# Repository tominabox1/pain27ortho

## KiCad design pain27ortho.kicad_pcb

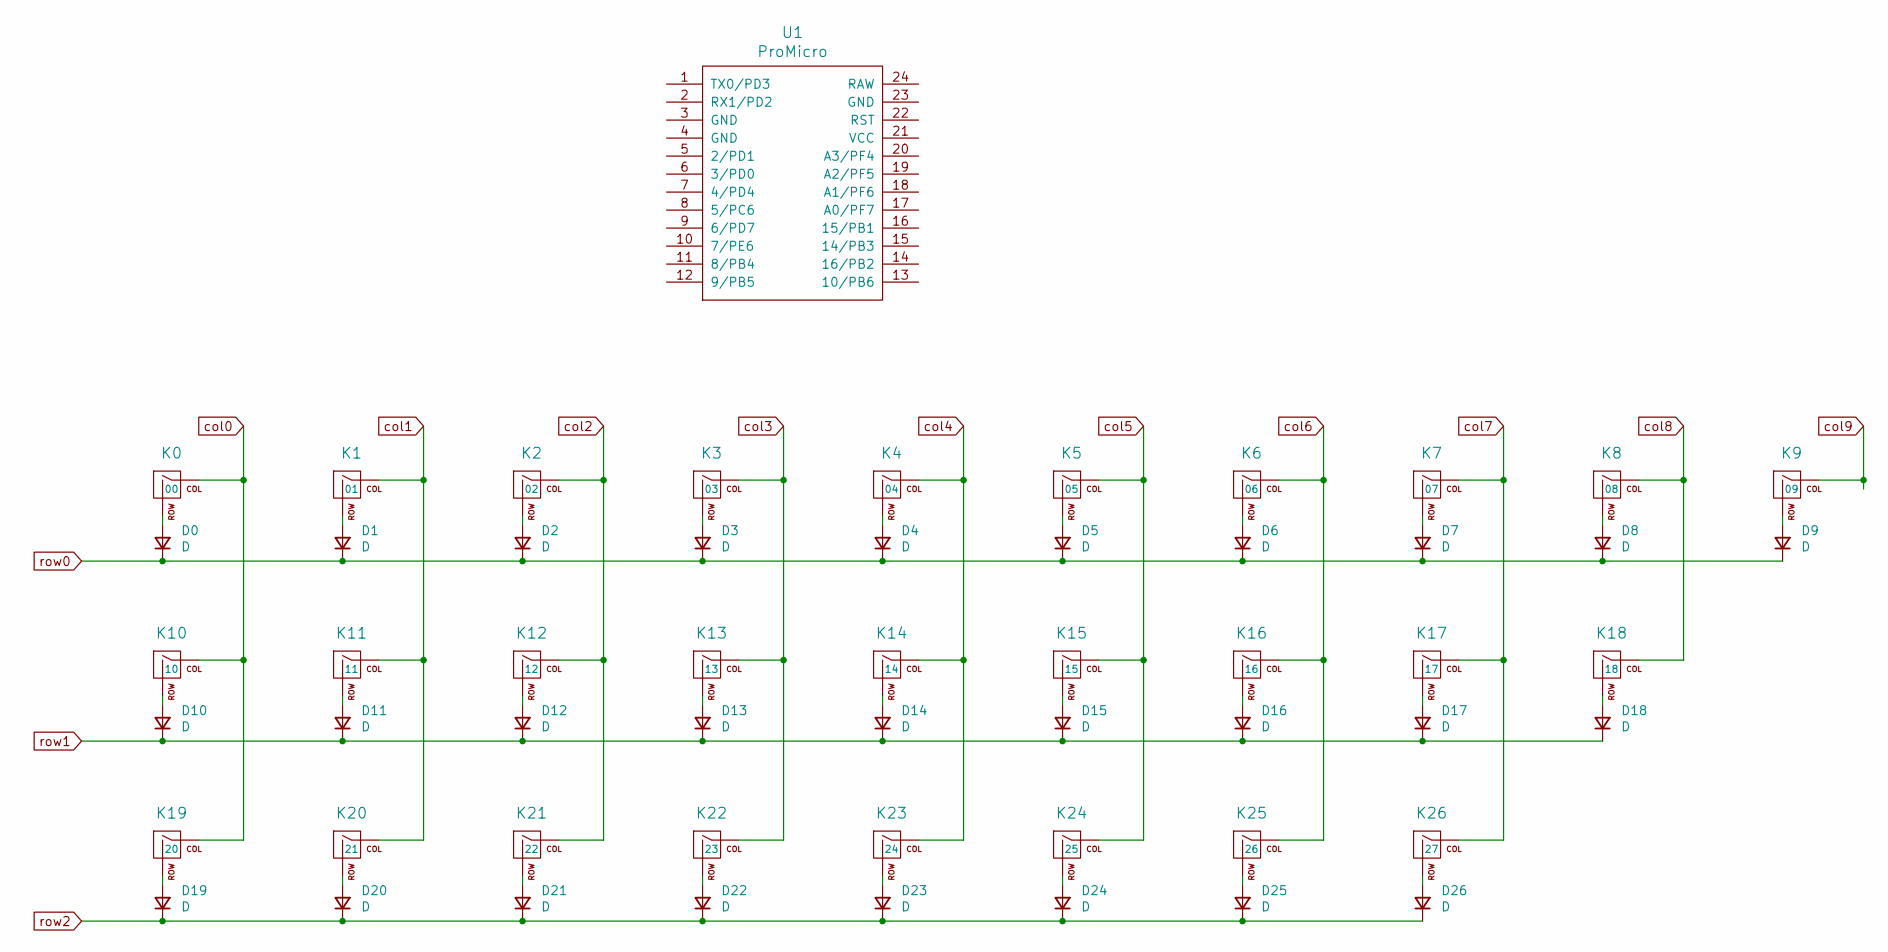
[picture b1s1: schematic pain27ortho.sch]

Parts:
D0, D1, D2, D3, D4, D5, D6, D7, D8, D9, D10, D11, D12, D13, D14, D15, D16, D17, D18, D19, D20, D21, D22, D23, D24, D25, D26: D; Diode-Hybrid-Back
K0, K1, K2, K3, K4, K5, K6, K7, K8, K9, K10, K11, K12, K13, K14, K15, K16, K17, K18, K19, K20, K21, K22, K23, K24, K25: 1U; MXOnly-1U-NoLED
K26: 6.25U; MXOnly-6.25U-NoLED
U1: ProMicro; ArduinoProMicro

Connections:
/Data: U1.8 (5/PC6); also elsewhere on the board
GND: U1.3 (GND), U1.4 (GND), U1.23 (GND); also elsewhere on the board
unnamed: D0.2 (A), K0.2 (ROW)
unnamed: D1.2 (A), K1.2 (ROW)
unnamed: D2.2 (A), K2.2 (ROW)
unnamed: D3.2 (A), K3.2 (ROW)
unnamed: D4.2 (A), K4.2 (ROW)
unnamed: D5.2 (A), K5.2 (ROW)
unnamed: D6.2 (A), K6.2 (ROW)
unnamed: D7.2 (A), K7.2 (ROW)
unnamed: D8.2 (A), K8.2 (ROW)
unnamed: D9.2 (A), K9.2 (ROW)
unnamed: D10.2 (A), K10.2 (ROW)
unnamed: D11.2 (A), K11.2 (ROW)
unnamed: D12.2 (A), K12.2 (ROW)
unnamed: D13.2 (A), K13.2 (ROW)
unnamed: D14.2 (A), K14.2 (ROW)
unnamed: D15.2 (A), K15.2 (ROW)
unnamed: D16.2 (A), K16.2 (ROW)
unnamed: D17.2 (A), K17.2 (ROW)
unnamed: D18.2 (A), K18.2 (ROW)
unnamed: D19.2 (A), K19.2 (ROW)
unnamed: D20.2 (A), K20.2 (ROW)
unnamed: D21.2 (A), K21.2 (ROW)
unnamed: D22.2 (A), K22.2 (ROW)
unnamed: D23.2 (A), K23.2 (ROW)
unnamed: D24.2 (A), K24.2 (ROW)
unnamed: D25.2 (A), K25.2 (ROW)
unnamed: D26.2 (A), K26.2 (ROW)
VCC: U1.21 (VCC); also elsewhere on the board
col0: K0.1 (COL), K10.1 (COL), K19.1 (COL), U1.20 (A3/PF4)
col1: K1.1 (COL), K11.1 (COL), K20.1 (COL), U1.18 (A1/PF6)
col2: K2.1 (COL), K12.1 (COL), K21.1 (COL), U1.13 (10/PB6)
col3: K3.1 (COL), K13.1 (COL), K22.1 (COL), U1.14 (16/PB2)
col4: K4.1 (COL), K14.1 (COL), K23.1 (COL), U1.15 (14/PB3)
col5: K5.1 (COL), K15.1 (COL), K24.1 (COL), U1.16 (15/PB1)
col6: K6.1 (COL), K16.1 (COL), K25.1 (COL), U1.17 (A0/PF7)
col7: K7.1 (COL), K17.1 (COL), K26.1 (COL), U1.11 (8/PB4)
col8: K8.1 (COL), K18.1 (COL), U1.10 (7/PE6)
col9: K9.1 (COL), U1.9 (6/PD7)
row0: D0.1 (K), D1.1 (K), D2.1 (K), D3.1 (K), D4.1 (K), D5.1 (K), D6.1 (K), D7.1 (K), D8.1 (K), D9.1 (K), U1.19 (A2/PF5)
row1: D10.1 (K), D11.1 (K), D12.1 (K), D13.1 (K), D14.1 (K), D15.1 (K), D16.1 (K), D17.1 (K), D18.1 (K), U1.12 (9/PB5)
row2: D19.1 (K), D20.1 (K), D21.1 (K), D22.1 (K), D23.1 (K), D24.1 (K), D25.1 (K), D26.1 (K)

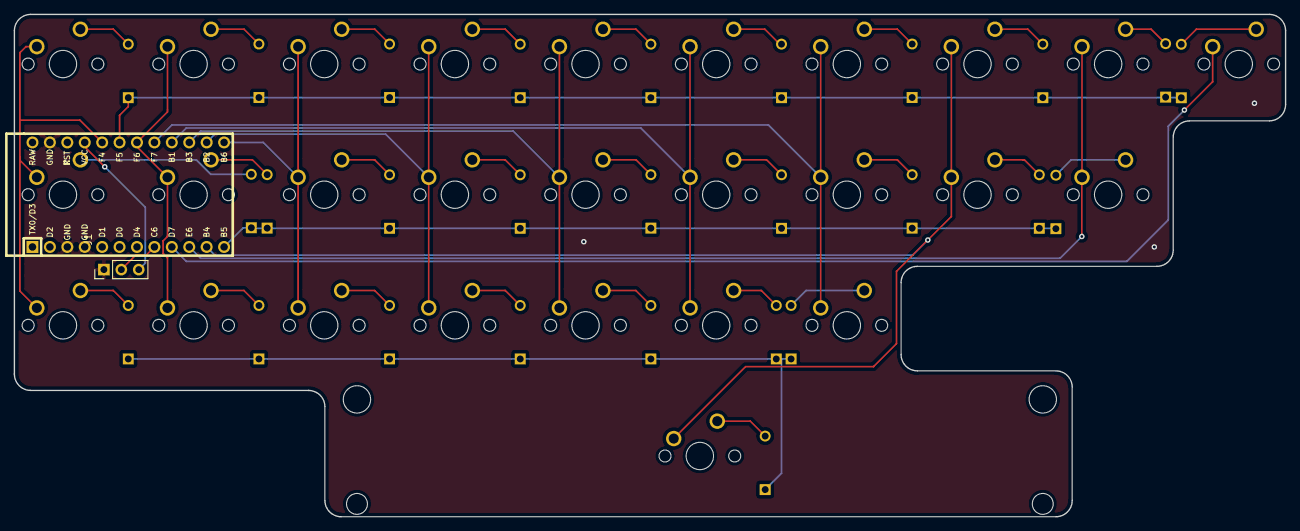
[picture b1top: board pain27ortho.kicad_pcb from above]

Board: 2 copper layers, 185.4 x 73.2 mm, 56 parts (0 on the bottom side), 43 nets.

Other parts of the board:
J1: Conn_01x03_Male; PinHeader_1x03_P2.54mm_Vertical

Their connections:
/Data: J1.2; also elsewhere on the board
GND: J1.1; also elsewhere on the board
VCC: J1.3; also elsewhere on the board
